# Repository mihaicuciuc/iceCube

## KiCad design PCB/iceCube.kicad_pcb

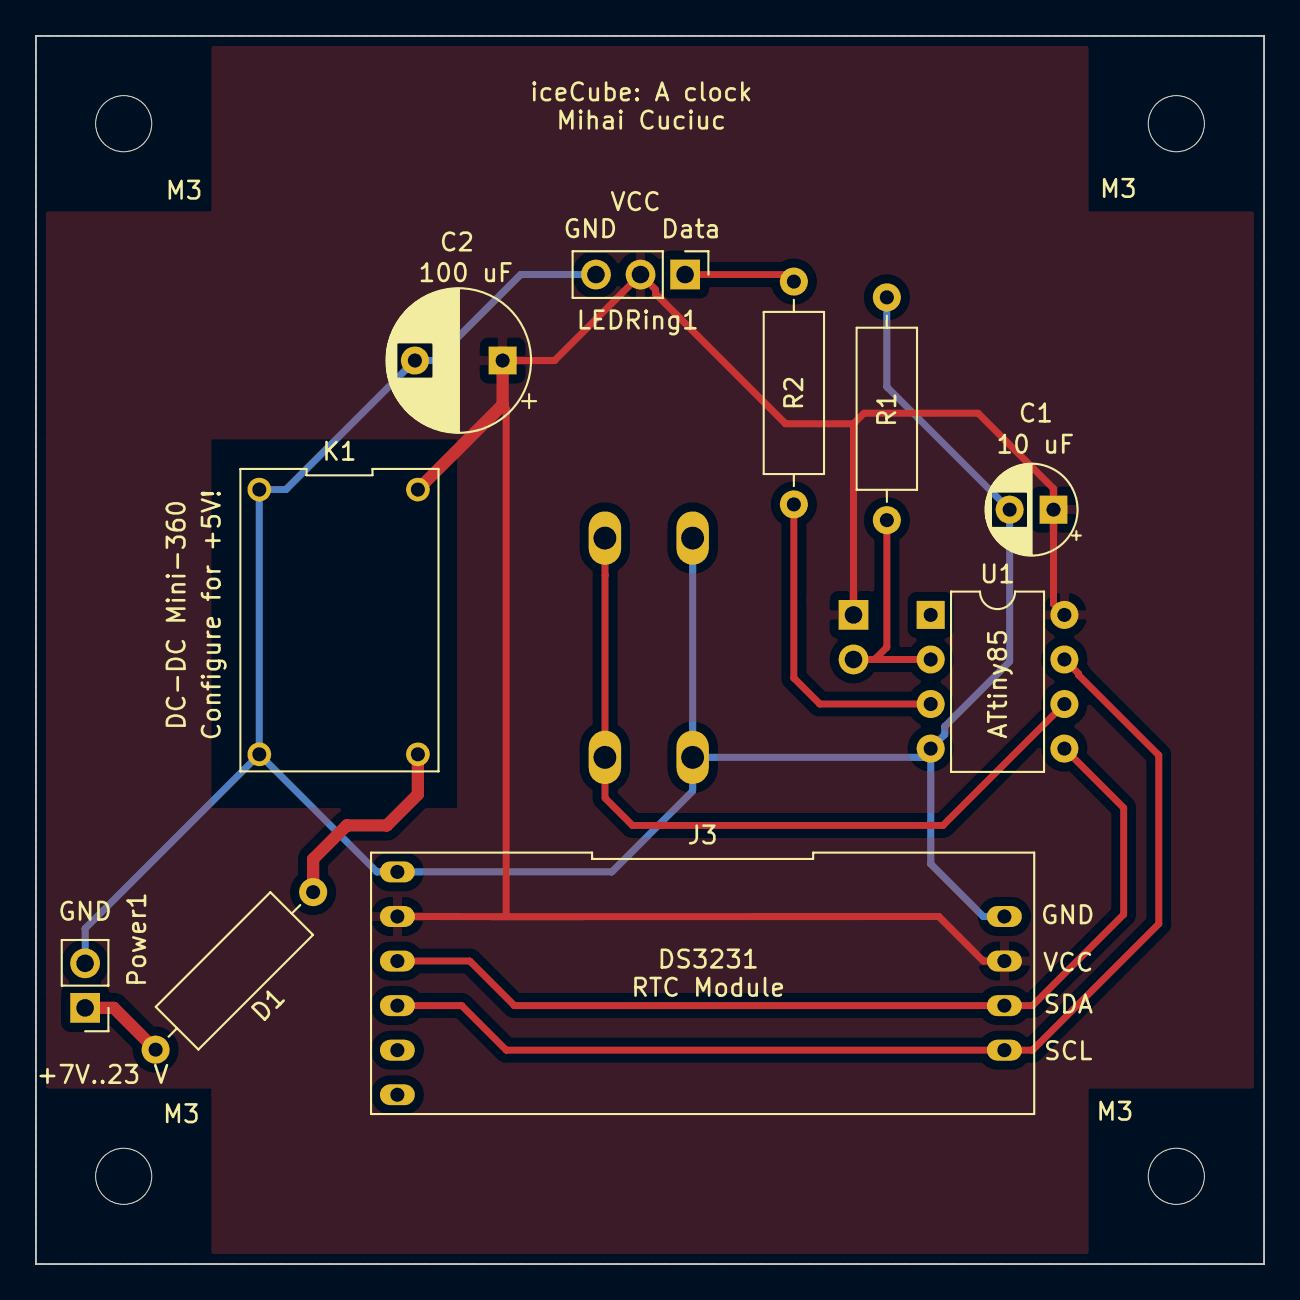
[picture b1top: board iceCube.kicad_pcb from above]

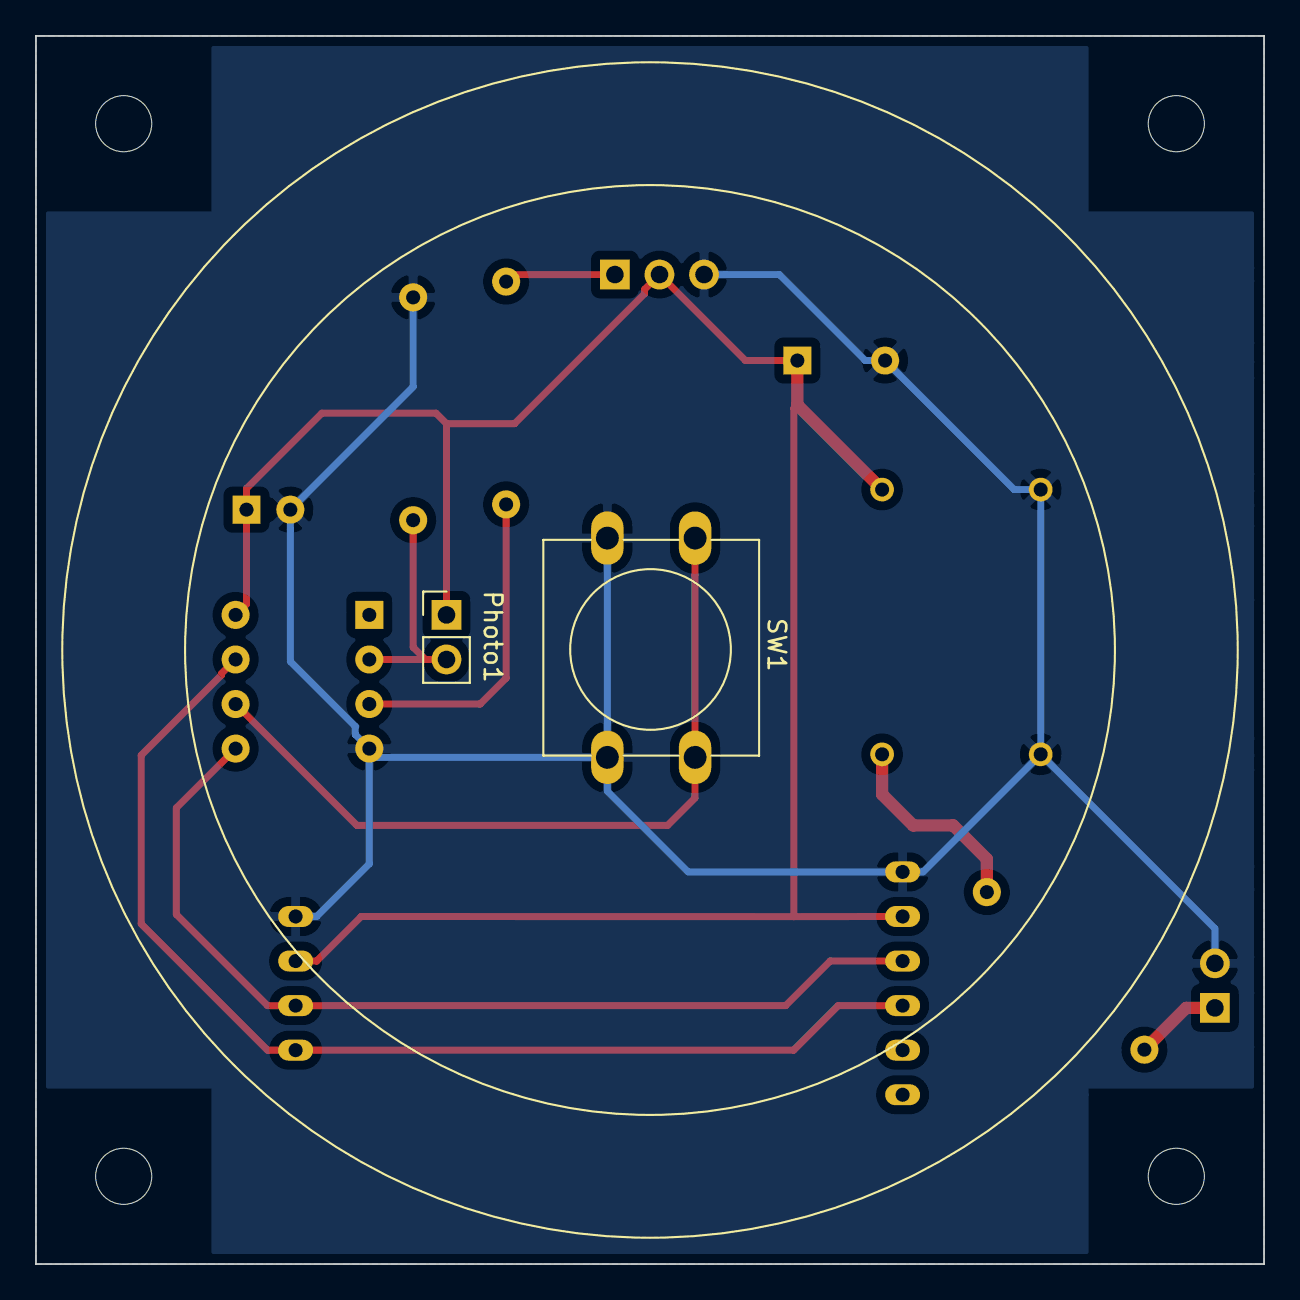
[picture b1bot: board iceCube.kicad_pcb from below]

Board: 2 copper layers, 70.0 x 70.0 mm, 16 parts (2 on the bottom side), 10 nets.

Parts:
C1: 10uF; CP_Radial_D5.0mm_P2.50mm
C2: 100uF; CP_Radial_D8.0mm_P5.00mm
D1: 1N4001; R_Axial_DIN0309_L9.0mm_D3.2mm_P12.70mm_Horizontal
J3: RTC; RTC_Module
K1: DC_DC_Mini-360
LEDRing1: LEDs; PinHeader_1x03_P2.54mm_Vertical
M3, M3#2, M3#3, M3#4: MountingHole_3.2mm_M3
Photo1: R_PHOTO; PinHeader_1x02_P2.54mm_Vertical
Power1: Power; PinHeader_1x02_P2.54mm_Vertical
R1: 75K; R_Axial_DIN0309_L9.0mm_D3.2mm_P12.70mm_Horizontal
R2: 300R; R_Axial_DIN0309_L9.0mm_D3.2mm_P12.70mm_Horizontal
SW1: SW_Push; SW_PUSH-12mm
U1: ATtiny85-20PU; DIP-8_W7.62mm

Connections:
+5V: C1.1, C2.1, J3.2, K1.4, LEDRing1.2, Photo1.1, U1.8
GNDD: C1.2, C2.2, J3.1, K1.1, K1.2, LEDRing1.3, Power1.2, R1.2, SW1.2, U1.4
unnamed: D1.1, K1.3
unnamed: D1.2, Power1.1
unnamed: J3.3, U1.5
unnamed: J3.4, U1.7
unnamed: LEDRing1.1, R2.1
unnamed: Photo1.2, R1.1, U1.2
unnamed: R2.2, U1.3
unnamed: SW1.1, U1.6

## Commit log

2020-05-11 initial upload
2020-05-16 updated color maps and minute setting behaviour
    precompiled hex
2020-05-16 updated color maps and minute setting behaviour
